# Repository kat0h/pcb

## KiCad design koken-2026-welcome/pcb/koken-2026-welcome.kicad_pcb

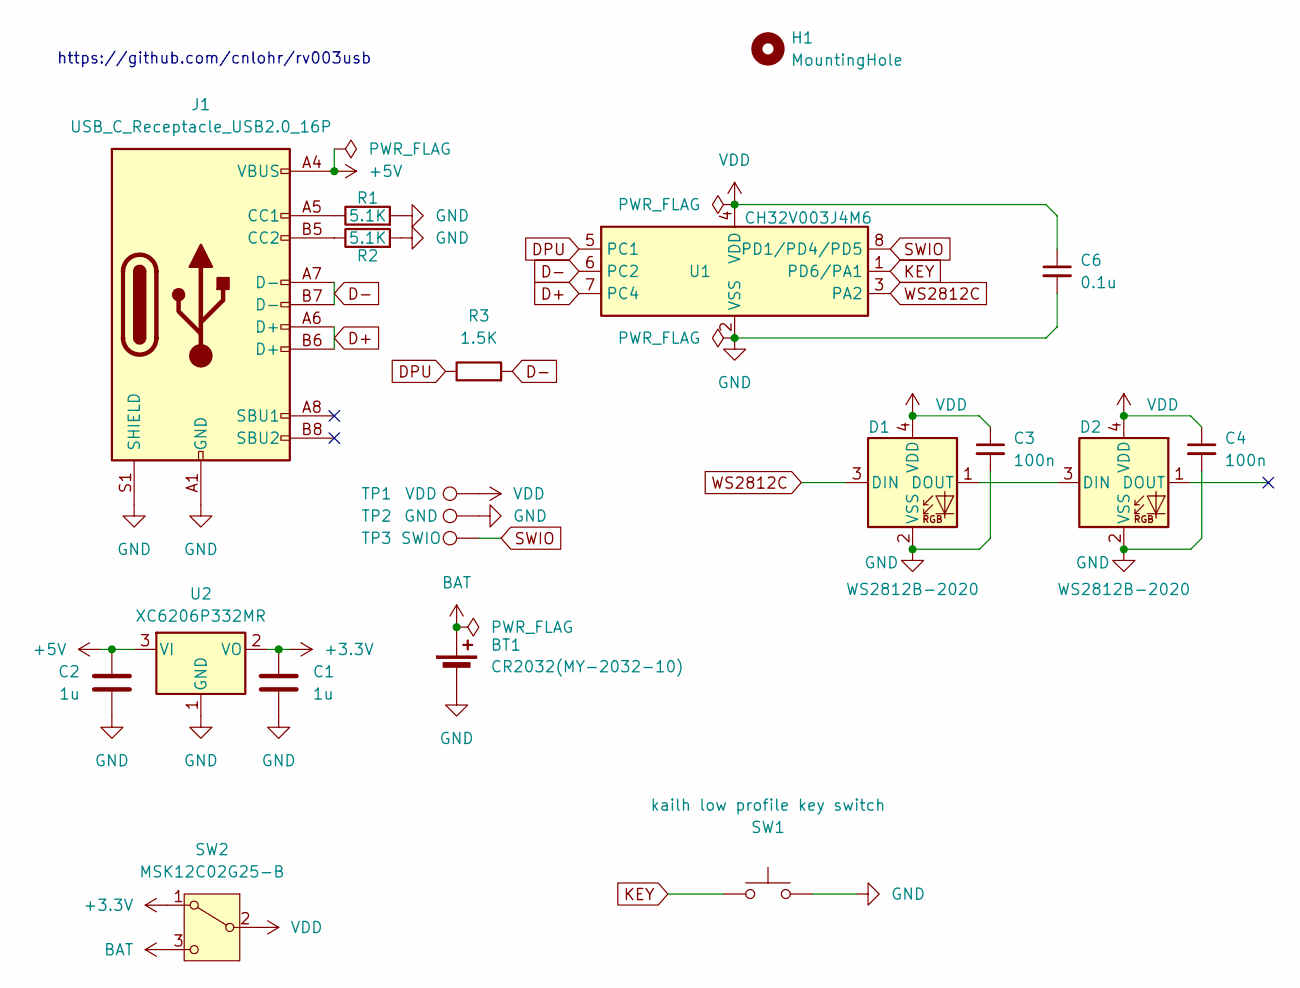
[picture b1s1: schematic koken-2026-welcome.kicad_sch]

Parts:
BT1: CR2032(MY-2032-10); MY-2032-10
C1, C2: 1u; C_0603_1608Metric_Pad1.08x0.95mm_HandSolder
C3, C4: 100n; C_0603_1608Metric_Pad1.08x0.95mm_HandSolder
C6: 0.1u; C_0603_1608Metric_Pad1.08x0.95mm_HandSolder
D1, D2: WS2812B-2020; LED_WS2812B-2020_PLCC4_2.0x2.0mm
H1: MountingHole; MountingHole_2.2mm_M2
J1: USB_C_Receptacle_USB2.0_16P; USB_C_Receptacle_GCT_USB4105-xx-A_16P_TopMnt_Horizontal
R1, R2: 5.1K; R_0603_1608Metric_Pad0.98x0.95mm_HandSolder
R3: 1.5K; R_0603_1608Metric_Pad0.98x0.95mm_HandSolder
SW1: kailh low profile key switch; SW_Kailh_Choc_V1
SW2: MSK12C02G25-B
TP1: VDD; TestPoint_Pad_D1.5mm
TP2: GND; TestPoint_Pad_D1.5mm
TP3: SWIO; TestPoint_Pad_D1.5mm
U1: CH32V003J4M6; JEITA_SOIC-8_3.9x4.9mm_P1.27mm
U2: XC6206P332MR; SOT-23-3

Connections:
+3.3V: C1.1, SW2.1 (A), U2.2 (VO)
+5V: C2.1, J1.A4 (VBUS), J1.A9 (VBUS), J1.B4 (VBUS), J1.B9 (VBUS), U2.3 (VI)
BAT: BT1.1 (+), SW2.3 (C)
D+: J1.A6 (D+), J1.B6 (D+), U1.7 (PC4)
D-: J1.A7 (D-), J1.B7 (D-), R3.2, U1.6 (PC2)
DPU: R3.1, U1.5 (PC1)
GND: BT1.2 (-), C1.2, C2.2, C3.2, C4.2, C6.2, D1.2 (VSS), D2.2 (VSS), J1.A1 (GND), J1.A12 (GND), J1.B1 (GND), J1.B12 (GND), J1.S1 (SHIELD), R1.2, R2.2, SW1.2, TP2.1, U1.2 (VSS), U2.1 (GND)
KEY: SW1.1, U1.1 (PD6/PA1)
unnamed: D1.1 (DOUT), D2.3 (DIN)
unnamed: J1.A5 (CC1), R1.1
unnamed: J1.B5 (CC2), R2.1
SWIO: TP3.1, U1.8 (PD1/PD4/PD5)
VDD: C3.1, C4.1, C6.1, D1.4 (VDD), D2.4 (VDD), SW2.2 (B), TP1.1, U1.4 (VDD)
WS2812C: D1.3 (DIN), U1.3 (PA2)

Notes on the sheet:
https://github.com/cnlohr/rv003usb

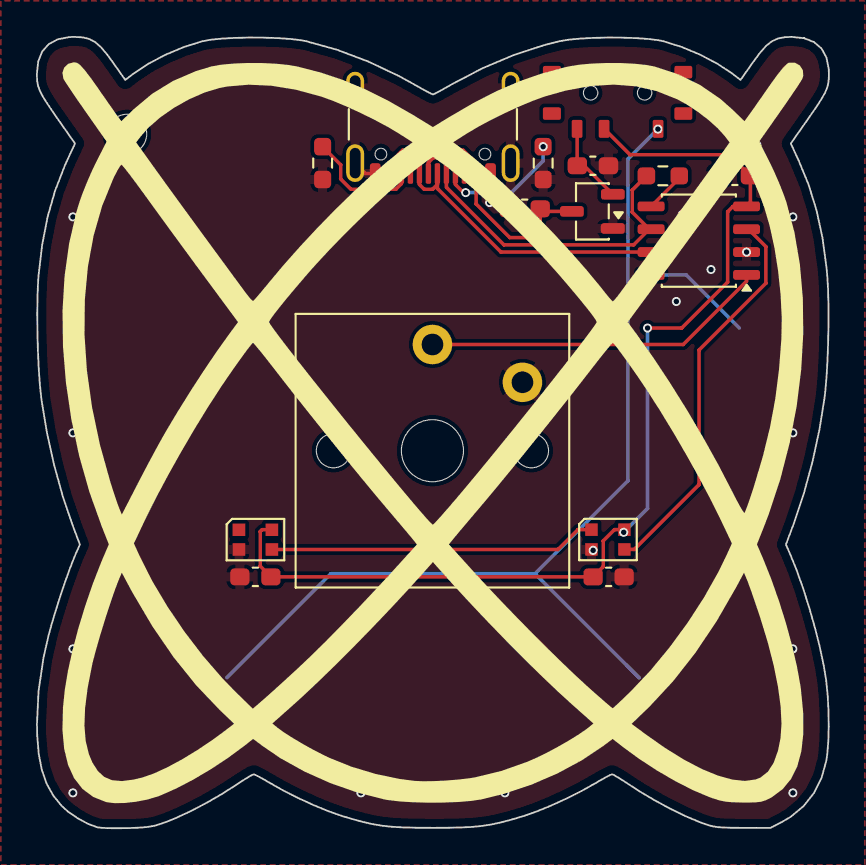
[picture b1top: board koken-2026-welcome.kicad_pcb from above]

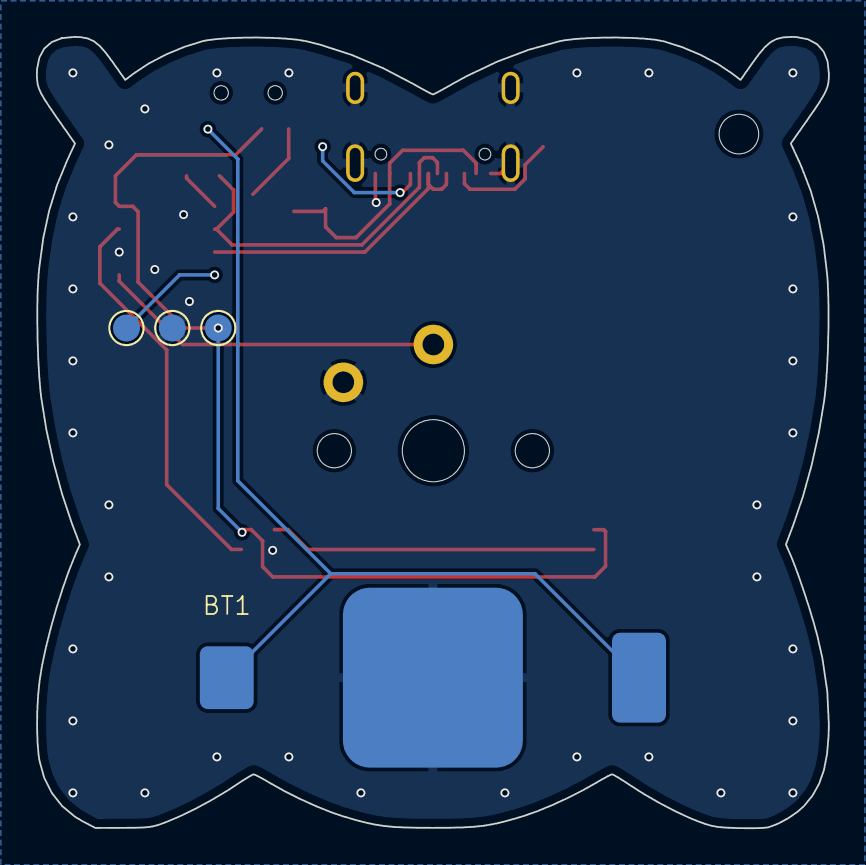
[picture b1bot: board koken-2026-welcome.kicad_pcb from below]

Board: 2 copper layers, 44.0 x 44.0 mm, 20 parts (4 on the bottom side), 14 nets.

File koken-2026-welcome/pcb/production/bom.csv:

Designator,Footprint,Quantity,Value,LCSC Part #
BT1,MY-2032-10,1,CR2032(MY-2032-10),
"C1, C2",0603,2,1u,
"C3, C4",0603,2,100n,
C6,0603,1,0.1u,
"D1, D2",LED_WS2812B-2020_PLCC4_2.0x2.0mm,2,WS2812B-2020,
J1,USB_C_Receptacle_GCT_USB4105-xx-A_16P_TopMnt_Horizontal,1,USB_C_Receptacle_USB2.0_16P,
"R1, R2",0603,2,5.1K,
R3,0603,1,1.5K,
SW1,SW_Kailh_Choc_V1,1,kailh low profile key switch,
SW2,MSK12C02G25-B,1,MSK12C02G25-B,
TP1,TestPoint_Pad_D1.5mm,1,VDD,
TP2,TestPoint_Pad_D1.5mm,1,GND,
TP3,TestPoint_Pad_D1.5mm,1,SWIO,
U1,JEITA_SOIC-8_3.9x4.9mm_P1.27mm,1,CH32V003J4M6,
U2,SOT-23-3,1,XC6206P332MR,

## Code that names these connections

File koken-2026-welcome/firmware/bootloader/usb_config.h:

#ifndef _USB_CONFIG_H
#define _USB_CONFIG_H

//Defines the number of endpoints for this device. (Always add one for EP0). For two EPs, this should be 3.  For one, 2.
#define ENDPOINTS 2

/*	
	CH32V003FUN DevBoard:
	PD3 D+
	PD4 D-
	PD5 D-_PU

	CH32V003J4M6:
	PC1 D+
	PC2 D-
	PC4 D-_PU
*/

#define USB_PORT C     // [A,C,D] GPIO Port to use with D+, D- and DPU
#define USB_PIN_DP 4   // [0-4] GPIO Number for USB D+ Pin
#define USB_PIN_DM 2   // [0-4] GPIO Number for USB D- Pin
#define USB_PORT_DPU C  // [A,C,D] Override GPIO Port for DPU
#define USB_PIN_DPU 1  // [0-7] GPIO for feeding the 1.5k Pull-Up on USB D- Pin; Comment out if not used / tied to 3V3!

#define RV003USB_OPTIMIZE_FLASH 1

#ifndef __ASSEMBLER__

#include <tinyusb_hid.h>

#ifdef INSTANCE_DESCRIPTORS
//Taken from http://www.usbmadesimple.co.uk/ums_ms_desc_dev.htm
static const uint8_t device_descriptor[] = {
	18, //Length
	1,  //Type (Device)
	0x00, 0x02, //Spec (bcdUSB)
	0x0, //Device Class
	0x0, //Device Subclass
	0x0, //Device Protocol  (000 = use config descriptor)
	0x08, //Max packet size for EP0 (This has to be 8 because of the USB Low-Speed Standard)
	0x09, 0x12, //ID Vendor   //TODO: register this in http://pid.codes/howto/ or somewhere.
	0x03, 0xb0, //ID Product
	0x00, 0x00, //ID Rev (bcdDevice)
	1, //Manufacturer string
	2, //Product string
	3, //Serial string
	1, //Max number of configurations
};


static const uint8_t special_hid_desc[] = { 
  HID_USAGE_PAGE ( HID_USAGE_PAGE_DESKTOP      )                 ,
  HID_USAGE      ( 0xff  )                 , // Needed?
  HID_COLLECTION ( HID_COLLECTION_APPLICATION )                 ,
    HID_REPORT_SIZE ( 8 ),
    HID_REPORT_COUNT ( 127 ) ,
    HID_REPORT_ID    ( 0xaa                                   )
    HID_USAGE        ( 0xff              ) ,
    HID_FEATURE      ( HID_DATA | HID_ARRAY | HID_ABSOLUTE    ) ,
  HID_COLLECTION_END
};


static const uint8_t config_descriptor[] = {  //Mostly stolen from a USB mouse I found.
	// configuration descriptor, USB spec 9.6.3, page 264-266, Table 9-10
	9, 					// bLength;
	2,					// bDescriptorType;
	0x22, 0x00,			// wTotalLength  	

	//34, 0x00, //for just the one descriptor
	
	0x01,					// bNumInterfaces (Normally 1)  (If we need an additional HID interface add here)
	0x01,					// bConfigurationValue
	0x00,					// iConfiguration
	0x80,					// bmAttributes (was 0xa0)
	0x64,					// bMaxPower (200mA)


	//HID THING
	9,					// bLength
	4,					// bDescriptorType
	0,			// bInterfaceNumber (unused, would normally be used for HID)
	0,					// bAlternateSetting
	1,					// bNumEndpoints
	0x03,					// bInterfaceClass (0x03 = HID)
	0x00,					// bInterfaceSubClass
	0xff,					// bInterfaceProtocol
	0,					// iInterface

	9,					// bLength
	0x21,					// bDescriptorType (HID)
	0x10,0x01,		//bcd 1.1
	0x00, //country code
	0x01, //Num descriptors
	0x22, //DescriptorType[0] (HID)
	sizeof(special_hid_desc), 0x00, //Descriptor length XXX This looks wrong!!!

	7, //endpoint descriptor (For endpoint 1)
	0x05, //Endpoint Descriptor (Must be 5)
	0x81, //Endpoint Address
	0x03, //Attributes
	0x08,	0x00, //Size
	0xff, //Interval
};


//Ever wonder how you have more than 6 keys down at the same time on a USB keyboard?  It's easy. Enumerate two keyboards!

#define STR_MANUFACTURER u"cnlohr"
#define STR_PRODUCT      u"rv003usb"
#ifndef STR_SERIAL
#define STR_SERIAL       u"NBTT" // Need to change to BOOT when we finally decide on a flashing mechanism.
#endif

struct usb_string_descriptor_struct {
	uint8_t bLength;
	uint8_t bDescriptorType;
	const uint16_t wString[];
};

const static struct usb_string_descriptor_struct string0 __attribute__((section(".rodata"))) = {
	4,
	3,
	{0x0409}
};
const static struct usb_string_descriptor_struct string1 __attribute__((section(".rodata")))  = {
	sizeof(STR_MANUFACTURER),
	3,
	STR_MANUFACTURER
};
const static struct usb_string_descriptor_struct string2 __attribute__((section(".rodata")))  = {
	sizeof(STR_PRODUCT),
	3,
	STR_PRODUCT
};
const static struct usb_string_descriptor_struct string3 __attribute__((section(".rodata")))  = {
	sizeof(STR_SERIAL),
	3,
	STR_SERIAL
};


// This table defines which descriptor data is sent for each specific
// request from the host (in wValue and wIndex).
const static struct descriptor_list_struct {
	uint32_t	lIndexValue;
	const uint8_t	*addr;
	uint8_t		length;
} descriptor_list[] __attribute__((section(".rodata"))) = {
	{0x00000100, device_descriptor, sizeof(device_descriptor)},
	{0x00000200, config_descriptor, sizeof(config_descriptor)},
	{0x00002200, special_hid_desc, sizeof(special_hid_desc)},
	{0x00000300, (const uint8_t *)&string0, 4},
	{0x04090301, (const uint8_t *)&string1, sizeof(STR_MANUFACTURER)},
	{0x04090302, (const uint8_t *)&string2, sizeof(STR_PRODUCT)},	
	{0x04090303, (const uint8_t *)&string3, sizeof(STR_SERIAL)}
};
#define DESCRIPTOR_LIST_ENTRIES ((sizeof(descriptor_list))/(sizeof(struct descriptor_list_struct)) )

#endif // INSTANCE_DESCRIPTORS

#endif // __ASSEMBLER__
#endif 

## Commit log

2025-12-09 koken-2026-welcome
2025-12-09 fix folder location
2025-12-09 add neopixel
2025-12-09 USBキーボードとNeopixel光るくん
2025-12-10 回路図完成
2025-12-10 assign footprint
2025-12-10 add c
2025-12-10 fix route
2026-02-13 move kicad project koken-2026-welcome
2026-02-13 add bootloader
    初回の発注からDPUピンを開けるために、1.5kを外して3.3vでプルアップした基板用のファームウェア
2026-02-13 お試しでPLLの動作を確認
    RCC_CFGR0のswビットを切り替えてPLLを付けたり切ったり 分周したり
2026-02-18 add readme.md to koken-2026-welcome firmware dir
2026-02-18 koken-2026-welcome メインのコードを整理
2026-02-18 koken-2026-welcome adcを使って電源電圧を取得できるように
2026-02-18 koken-2026-welcome 電圧源に応じてLEDの光らせ方を制御
2026-02-18 koken-2026-welcome format code
2026-02-18 koken-2026-welcome 新しい基板の配線を設計
    キースイッチをkailhに
    ws2812を2個に
    ldoを変更
2026-02-20 基板試作2号
2026-03-05 initial dev environment
2026-03-05 void server
2026-04-03 新歓基板ファームウェアを軽く修正
    2026年の新歓基板用にファームウェアのボタンの動作を変更
2026-04-03 bootloaderの動作確認
    configurebootloaderを使うことで、書き込んだブートローダーを利用できるようになった
2026-04-03 bootloader 完成
    きちんと利用できるbootloaderが完成した
2026-04-03 ファームウェアを簡略化
2026-04-05 バッテリー駆動時のコードを記述
    ボタンを押すと明るく光る
2026-04-05 delay_msの代わりにsleepするように
2026-04-05 コードを整理
2026-04-05 USB動作時にボタン入力を判定する
2026-04-05 単押しと長押しを区別
2026-04-05 モールス符号で打てるように
2026-04-06 とりあえず配布用ファームv1
